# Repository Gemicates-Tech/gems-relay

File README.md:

# gems-relay
The Smart Relay V_0.3 is a versatile and intelligent relay module designed for use in home automation.

Admin:
Elangovan M

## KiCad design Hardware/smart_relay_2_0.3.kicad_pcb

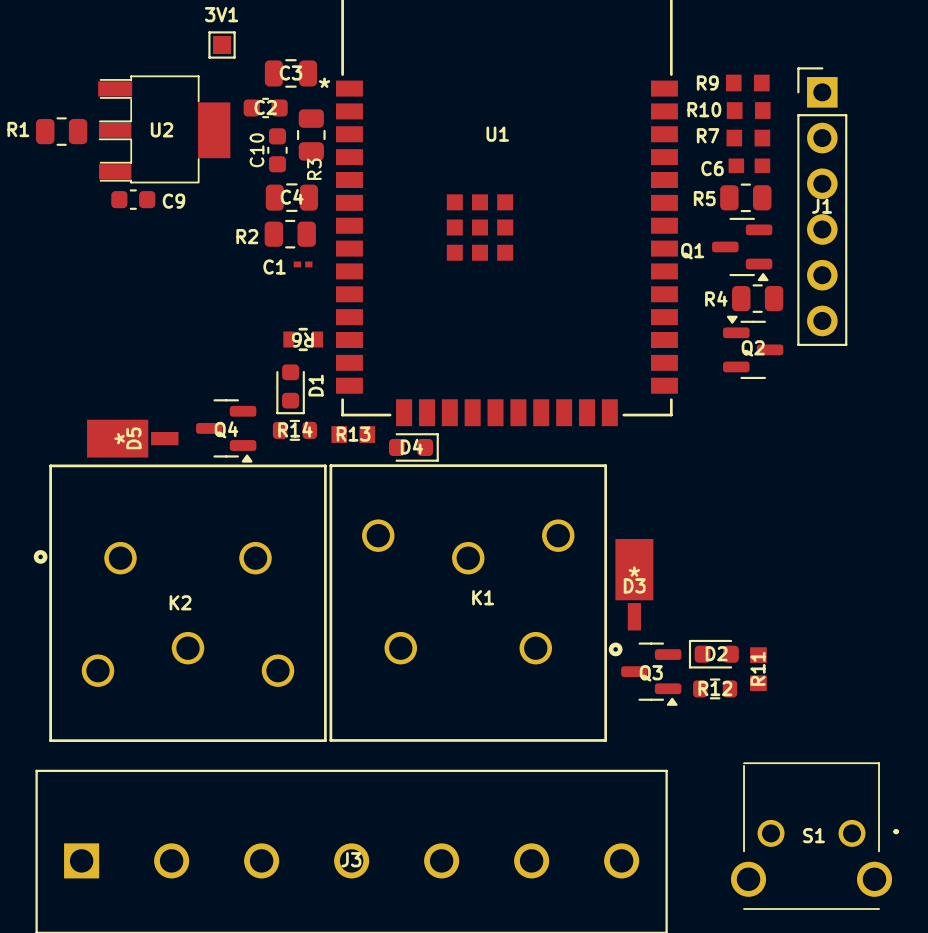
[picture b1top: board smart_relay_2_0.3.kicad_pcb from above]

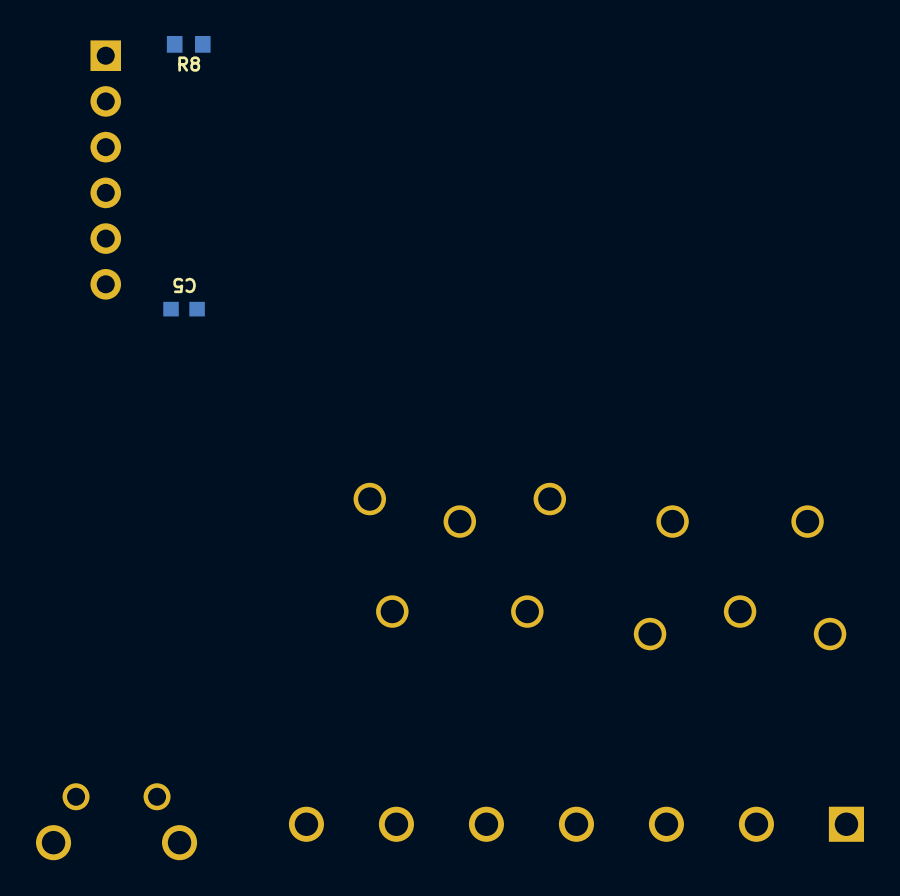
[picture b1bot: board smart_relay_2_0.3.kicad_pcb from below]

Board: 2 copper layers, 39 parts (2 on the bottom side), 30 nets, no tracks yet.

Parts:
3V1: TP4; TestPoint_Pad_1.0x1.0mm
C1: 1uF; CAP_CC0201_YAG
C2: 22uF/10V; C_0603_1608Metric
C3, C4: 0.1uF/50V; C_0805_2012Metric
C5, C6: 10uF; G-188_MUR
C9, C10: 1uF; C_0603_1608Metric
D1, D2, D4: LED; LED_0603_1608Metric
D3, D5: D_Schottky; CR_POWERMITE_457-04_ONS
J1: UART1 PROGRAMMER; PinHeader_1x06_P2.54mm_Vertical
J3: Conn_01x07_Pin; CUI_TB001-500-07BE
K1, K2: PB766-ND; RELAY5_1415030_TEC
Q1, Q2, Q3, Q4: NPN; SOT-23
R1, R2, R3, R4, R5: 10K; R_0805_2012Metric
R6: 100 ohm; RES_RK73B_1J_KOA
R7, R8, R9, R10: 2k; RESC1608X55N
R11, R13: 10K; RESC1608X55N
R12, R14: 649E; R_0603_1608Metric
S1: PTS645VL582LFS
U1: ESP32-WROOM-32E-N8; ESP32­WROOM­32E_EXP
U2: Reg linear 3.3v; IC REG LINEAR 3.3V 1A SOT223-4

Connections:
5V: C9.1, D3.1 (K), D5.1 (K), K1.A1, K2.A1, U2.3 (IN)
+3V3: 3V1.1, C2.1, C3.1, C10.1, J1.1, R1.1, R3.1, R9.2, R10.2, U1.2 (3V3), U2.2 (OUTPUT)
/MCU/DTR: J1.6, Q2.3 (C), R4.1
/MCU/EN: C4.1, Q1.3 (C), R3.2, U1.3 (EN)
/MCU/IO0: Q2.2 (E), U1.25 (IO0)
/MCU/IP_PROV_SWITCH: C1.1, R2.1, U1.6 (IO34)
/MCU/IP_SWITCH_1: C5.1, R8.2, U1.27 (IO16)
/MCU/IP_SWITCH_2: C6.1, R7.2, U1.28 (IO17)
/MCU/OP_LED: R6.1, U1.12 (IO27)
/MCU/RTS: J1.5, Q1.2 (E), R5.1
/MCU/RX: J1.3, U1.34 (RXD0)
/MCU/SWITCH_1: R8.1, R9.1
/MCU/SWITCH_2: R7.1, R10.1
/MCU/TX: J1.4, U1.35 (TXD0)
/Power section/K1_OP: J3.3, K2.12
/Power section/K2_OP: J3.4, K1.12
/Power section/OP_RELAY_1: R13.2, R14.2
/Power section/OP_RELAY_2: R11.2, R12.2
GND: C1.2, C2.2, C3.2, C4.2, C5.2, C6.2, C9.2, C10.2, D1.1 (K), D2.1 (K), D4.1 (K), J1.2, J3.7, K1.14, K2.14, Q3.2 (E), Q4.2 (E), S1.2, S1.MH1, S1.MH2, U1.1 (GND), U1.15 (GND), U1.38 (GND), U1.39 (GND), U1.40 (GND), U1.41 (GND), U1.42 (GND), U1.43 (GND), U1.44 (GND), U1.45 (GND), U1.46 (GND), U1.47 (GND), U2.1 (GND)
LINE: J3.1, K1.11, K2.11
unnamed: D1.2 (A), R6.2
unnamed: D2.2 (A), R11.1
unnamed: D3.2 (A), K1.A2, Q3.3 (C)
unnamed: D4.2 (A), R13.1
unnamed: D5.2 (A), K2.A2, Q4.3 (C)
unnamed: Q1.1 (B), R4.2
unnamed: Q2.1 (B), R5.2
unnamed: Q3.1 (B), R12.1
unnamed: Q4.1 (B), R14.1
unnamed: R1.2, R2.2, S1.1

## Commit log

2025-02-14 Add the new relay schematic and update footprients
2025-02-14 test commit by elangovan
2025-02-15 strarted PCB placement for Smart relay v0_3
